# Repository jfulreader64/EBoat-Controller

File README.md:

# EBoat-Controller
DC-DC, Precharge, and accelerator control for an electric boat project

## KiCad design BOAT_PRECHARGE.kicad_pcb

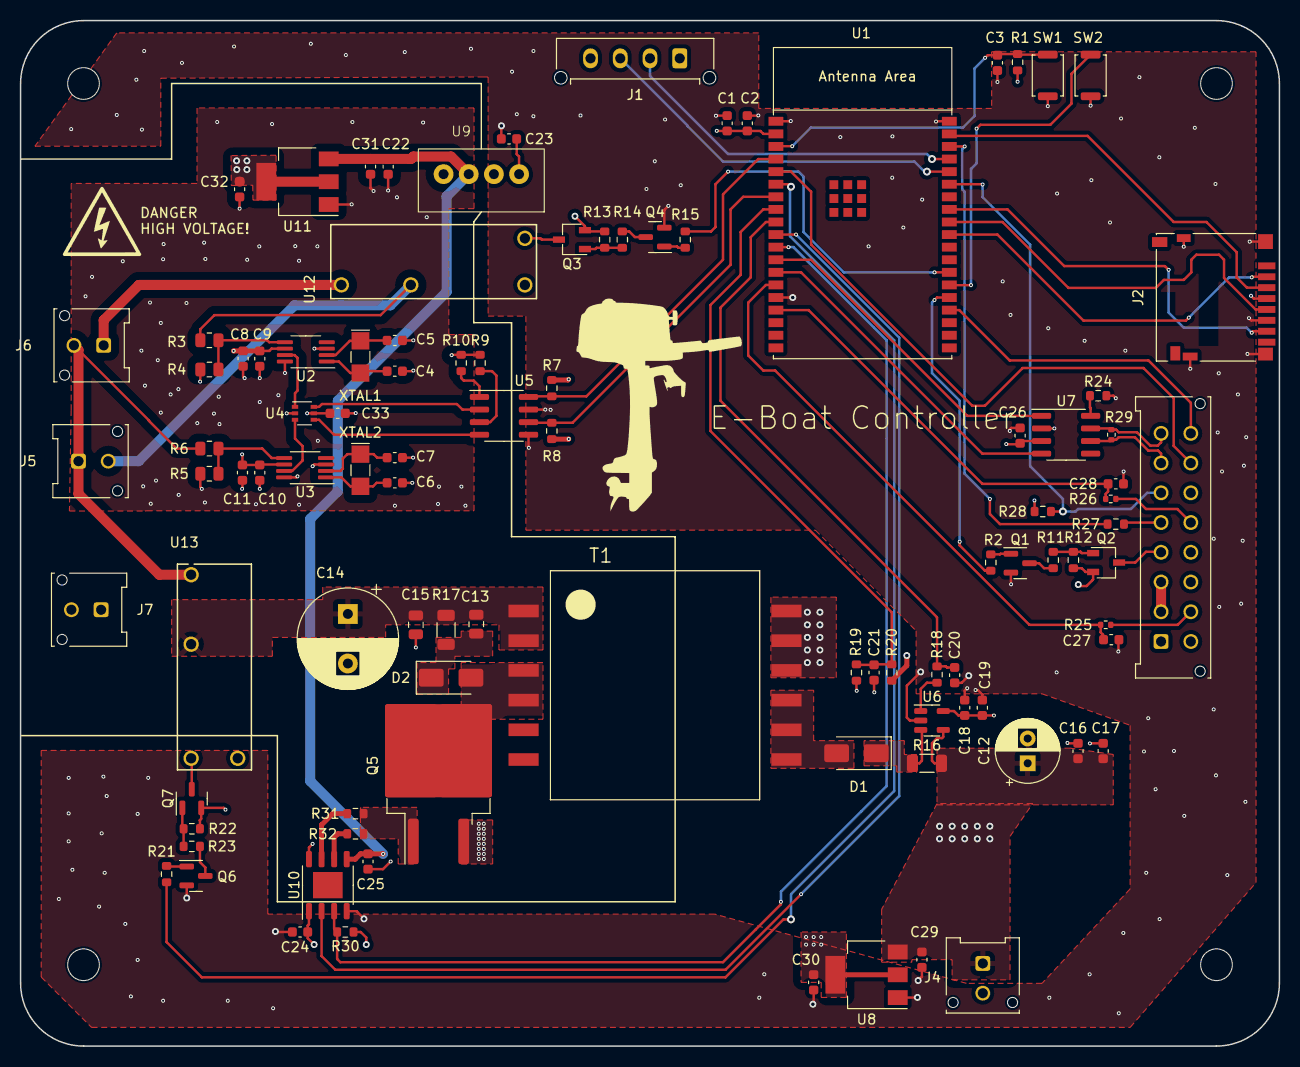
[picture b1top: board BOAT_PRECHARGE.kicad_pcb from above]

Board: 4 copper layers, 127.0 x 103.5 mm, 104 parts (0 on the bottom side), 74 nets.

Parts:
C1, C16, C17, C30, C32: 22u; C_0603_1608Metric
C2, C9, C11: .1u; C_0603_1608Metric
C3, C19: 1u; C_0603_1608Metric
C4, C5, C6, C7: 4.7p; C_0603_1608Metric
C8, C10, C29, C31: 10u; C_0603_1608Metric
C12: 150u; CP_Radial_D6.3mm_P2.50mm
C13: 2.2n; C_0805_2012Metric
C14: 47u; CP_Radial_D10.0mm_P5.00mm
C15: 2.2u; C_0805_2012Metric
C18, C24, C25, C26, C33: 100n; C_0603_1608Metric
C20, C21: 1n; C_0603_1608Metric
C22, C23, C27, C28: 2.2u; C_0603_1608Metric
D1, D2: SK220A; D_SMA
G: LOGO
H1, H2, H3, H4: MountingHole; MountingHole_3.2mm_M3
J1: Conn_01x04; Molex_Micro-Fit_3.0_43650-0415_1x04_P3.00mm_Vertical
J2: Micro_SD_Card_Det2; microSD_HC_Hirose_DM3D-SF
J3: Conn_01x16_Pin; Molex_Micro-Fit_3.0_43045-1612_2x08_P3.00mm_Vertical
J4, J5, J6: Conn_01x02_Pin; Molex_Micro-Fit_3.0_43045-0212_2x01_P3.00mm_Vertical
J7: Conn_01x01_Pin; Molex_Micro-Fit_3.0_43045-0212_2x01_P3.00mm_Vertical
Q1, Q4, Q6: MMBT5551LT1G; SOT-23
Q2, Q3: DMG2305UX-13; TSOT-23
Q5: FDB44N25TM; TO-263-2
Q7: DMG2305UX-13; SOT-23
R1, R7, R8, R11, R12, R13, R14, R22, R23, R24, R28, R30: 10k; R_0603_1608Metric
R2, R15, R21: 470; R_0603_1608Metric
R3, R6: 100k; R_0805_2012Metric
R4, R5: 4k7; R_0805_2012Metric
R9, R10: 330; R_0603_1608Metric
R16: 5m; R_1206_3216Metric
R17: 56k; R_1206_3216Metric
R18: 1k; R_0603_1608Metric
R19: 22k; R_0603_1608Metric
R20: 100k; R_0603_1608Metric
R25, R26: 1k; R_0402_1005Metric
R27: 100; R_0603_1608Metric
R29: 120; R_0402_1005Metric
R31, R32: 22; R_0603_1608Metric
SW1: SKRKAHE020; SW_Push_SPST_NO_Alps_SKRK
SW2: SW_DIP_x01; SW_Push_SPST_NO_Alps_SKRK
T1: 750311797; EFD20_SMT_H_12PIN__4275_
U1: ESP32-WROVER-IE; ESP32-WROVER-E
U2, U3: AD7740YRMZ; MSOP-8_3x3mm_P0.65mm
U4: 74LVC2G14; SOT-363_SC-70-6
U5: VOD217T; SOIC-8_3.9x4.9mm_P1.27mm
U6: INA180A3IDBVR; SOT-23-5
U7: SN65HVD230; SOIC-8_3.9x4.9mm_P1.27mm
U8: AZ1117-3.3; SOT-223-3_TabPin2
U9: B1212S-1WR3
U10: Infineon_PG-DSO-8-27_3.9x4.9mm_EP2.65x3mm
U11: AZ1117-5.0; SOT-223-3_TabPin2
U12, U13: ALDP112W; PAN_ALD_PAN
XTAL1, XTAL2: SC32S-7PF20PPM; Crystal_SMD_G8-2Pin_3.2x1.5mm_HandSoldering

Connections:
+3V3: C1.1, C2.1, C18.1, C19.1, C24.1, C26.1, C30.1, J1.1, J2.4 (VDD), J3.9, J3.12, R1.1, R7.1, R8.1, R28.2, R30.1, U1.2 (3V3), U6.5 (VS), U7.3 (VCC), U8.2 (VO), U10.1 (VCC1)
+5VP: C8.2, C9.2, C10.2, C11.2, C32.1, C33.1, R9.1, R10.1, U2.6 (VDD), U3.6 (VDD), U4.5 (VCC), U11.2 (VO)
+12P: C22.1, C25.1, C31.1, U9.3 (Vout), U10.5 (VCC2), U11.3 (VI)
+12V: C12.1, C16.2, C17.2, C23.1, C29.1, J4.1, Q2.2, Q3.2, Q7.2, R12.2, R13.2, R16.2, R20.2, R22.2, U6.4 (IN-), U8.3 (VI), U9.1 (Vin)
/DC-DC/DCDC_Relay_Drive: Q7.3, U13.3
/Precharge/Fbatt: U4.6, U5.2 (CATHODE)
/Precharge/Fesc: U4.4, U5.4 (CATHODE)
/Precharge/Precharge_Relay_Drive: Q3.3, U12.4
CAN_+: J3.8, R29.1, U7.7 (CANH)
CAN_-: J3.7, R29.2, U7.6 (CANL)
CAN_RX: U1.13 (MTMS/GPIO14/ADC2_CH6), U7.4 (R)
CAN_TX: U1.12 (ADC2_CH7/GPIO27), U7.1 (D)
Contactor Side: J5.2, R3.2, U12.2
Contactor+: J3.2, J3.3
Contactor_Control: R2.2, U1.24 (ADC2_CH2/GPIO2)
DCDC_Control: R21.2, U1.6 (GPIO34/ADC1_CH6)
DCDC_Curr: C20.1, R18.2, U1.9 (32K_XN/GPIO33/ADC1_CH5)
DCDC_GATE_DRIVE: U1.10 (DAC_1/ADC2_CH8/GPIO25), U10.2 (IN+)
DCDC_Vsense: C21.1, R19.2, R20.1, U1.8 (32K_XP/GPIO32/ADC1_CH4)
GND1: C4.1, C5.1, C6.1, C7.1, C8.1, C9.1, C10.1, C11.1, C14.2, C15.2, C22.2, C25.2, C31.2, C32.2, C33.2, J7.1, Q5.3 (S), R4.1, R5.1, U2.3 (GND), U2.8 (BUF), U3.3 (GND), U3.8 (BUF), U4.2 (GND), U9.4 (GND_1), U10.8 (VEE2), U11.1 (GND)
GPIO1: J3.15, U1.5 (SENSOR_VN/GPIO39/ADC1_CH3)
GPIO2: J3.16, U1.23 (MTDO/GPIO15/ADC2_CH3)
unnamed: C13.1, C14.1, C15.1, R17.2, T1.1, T1.2, U13.2
unnamed: D1.2 (A), T1.7, T1.8, T1.9
unnamed: D1.1 (K), R16.1, U6.3 (IN+)
unnamed: D2.2 (A), Q5.2 (D), T1.3, T1.4
unnamed: C13.2, D2.1 (K), R17.1
unnamed: J1.2, U1.35 (U0TXD/GPIO1)
unnamed: J1.3, U1.34 (U0RXD/GPIO3)
unnamed: J6.1, U12.1
unnamed: Q1.1 (B), R2.1
unnamed: Q1.3 (C), R11.1
unnamed: Q2.1, R11.2, R12.1
unnamed: Q3.1, R13.1, R14.2
unnamed: Q4.1 (B), R15.1
unnamed: Q4.3 (C), R14.1
unnamed: Q5.1 (G), R31.2, R32.2
unnamed: Q6.1 (B), R21.1
unnamed: Q6.3 (C), R23.1
unnamed: Q7.1, R22.1, R23.2
unnamed: R9.2, U5.3 (ANODE)
unnamed: R10.2, U5.1 (ANODE)
unnamed: C3.1, R1.2, SW1.2, U1.3 (EN/CHIP_PU)
unnamed: SW2.1, U1.25 (GPIO0/BOOT/ADC2_CH1)
unnamed: R27.1, U1.36 (GPIO22)
unnamed: C28.1, R26.2, U1.16 (MTCK/GPIO13/ADC2_CH4)
unnamed: C27.1, R25.2, U1.14 (MTDI/GPIO12/ADC2_CH5)
unnamed: C5.2, U2.2 (CLKIN), XTAL1.1
unnamed: C4.2, U2.1 (CLKOUT), XTAL1.2
unnamed: U2.7 (FOUT), U4.1
unnamed: R3.1, R4.2, U2.5 (VIN)
unnamed: C7.2, U3.2 (CLKIN), XTAL2.1
unnamed: C6.2, U3.1 (CLKOUT), XTAL2.2
unnamed: U3.7 (FOUT), U4.3
unnamed: R5.2, R6.1, U3.5 (VIN)
unnamed: R18.1, U6.1 (OUT)
unnamed: R24.1, U7.8 (Rs)
unnamed: R32.1, U10.6 (OUTH)
unnamed: R31.1, U10.7 (OUTL)
Pot1: J3.10, R25.1
Pot2: J3.13, R26.1
RTN: C1.2, C2.2, C3.2, C12.2, C16.1, C17.1, C18.2, C19.2, C20.2, C21.2, C23.2, C24.2, C26.2, C27.2, C28.2, C29.2, C30.2, J1.4, J2.6 (VSS), J2.11 (SHIELD), J3.1, J3.11, J3.14, J4.2, Q1.2 (E), Q4.2 (E), Q6.2 (E), R19.1, R24.2, SW1.1, SW2.2, T1.10, T1.11, T1.12, U1.1 (GND), U1.15 (GND), U1.38 (GND), U5.5 (EMITTER), U5.7 (EMITTER), U6.2 (GND), U7.2 (GND), U8.1 (GND), U9.2 (GND), U10.4 (GND), U12.3, U13.4
Relay_Control: R15.2, U1.26 (ADC2_CH0/GPIO4)
SDButton_p: J3.4, Q2.3
SPI_MOSI: J2.3 (CMD), U1.37 (GPIO23)
SPI_MOSO: J2.7 (DAT0), U1.31 (GPIO19)
SPI_NSS: J2.2 (DAT3/CD), U1.29 (GPIO5)
SPI_SCK: J2.5 (CLK), U1.30 (GPIO18)
Status_LED: J3.5, R27.2
Sw_ENABLE: R30.2, U1.11 (DAC_2/ADC2_CH9/GPIO26), U10.3 (IN-)
Vdrive: J5.1, J6.2, R6.2, U13.1
Vsense_Batt: R7.2, U1.4 (SENSOR_VP/GPIO36/ADC1_CH0), U5.8 (COLLECTOR)
Vsense_Esc: R8.2, U1.7 (GPIO35/ADC1_CH7), U5.6 (COLLECTOR)
Wake: J3.6, R28.1, U1.33 (GPIO21)
